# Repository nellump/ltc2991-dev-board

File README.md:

# LTC2991 Development Board

A simple printed circuit board that makes it easy to plug the
surface-mount (MSOP-16) [LTC2991][1] into a common breadboard.

[1]: http://www.linear.com/product/LTC2991

*NB: This project is a work in progress!  Schematic and PCB layout for
Rev. B design are complete; assembly is pending.*

## Features

* A pair of pin headers for each of the LTC2991's address lines.
  Jumpering the pins on any given address line connects that line to
  ground.
* Pads suitable for a current-sensing shunt resistor (1206 SMD),
  connected across the V1 and V2 terminals of the LTC2991, and pads
  for a 1x2 pin header to connect said shunt to the outside world.
* Pads suitable for a temperature-sensing, diode-connected NPN BJT
  (SOT-23 SMD), connected across the V3 and V4 terminals of the
  LTC2991, and a filter capactitor for said transistor.

## Caveats

There seems to be no such thing as a breadboard standard.  This PCB
was designed to work with an [R.S.R.-branded breadboard][2].  It
features a 0.100" pin pitch, and an approx. 0.300" gap down the middle
of the board.

[2]: http://rsrelectronics.com/breadboards.html

## Changelog

1. Rev. A: Initial design.
2. Rev. B:
  * Added two-pin header for measurement of external current source
    via on-board shunt resistor (both optional).
  * Added filter capacitor for IC power.
  * Added filter capacitor for temperature-sensing transistor (both
    optional).
  * Placed noise-shielding traces around temperature-sensing
    transistor.

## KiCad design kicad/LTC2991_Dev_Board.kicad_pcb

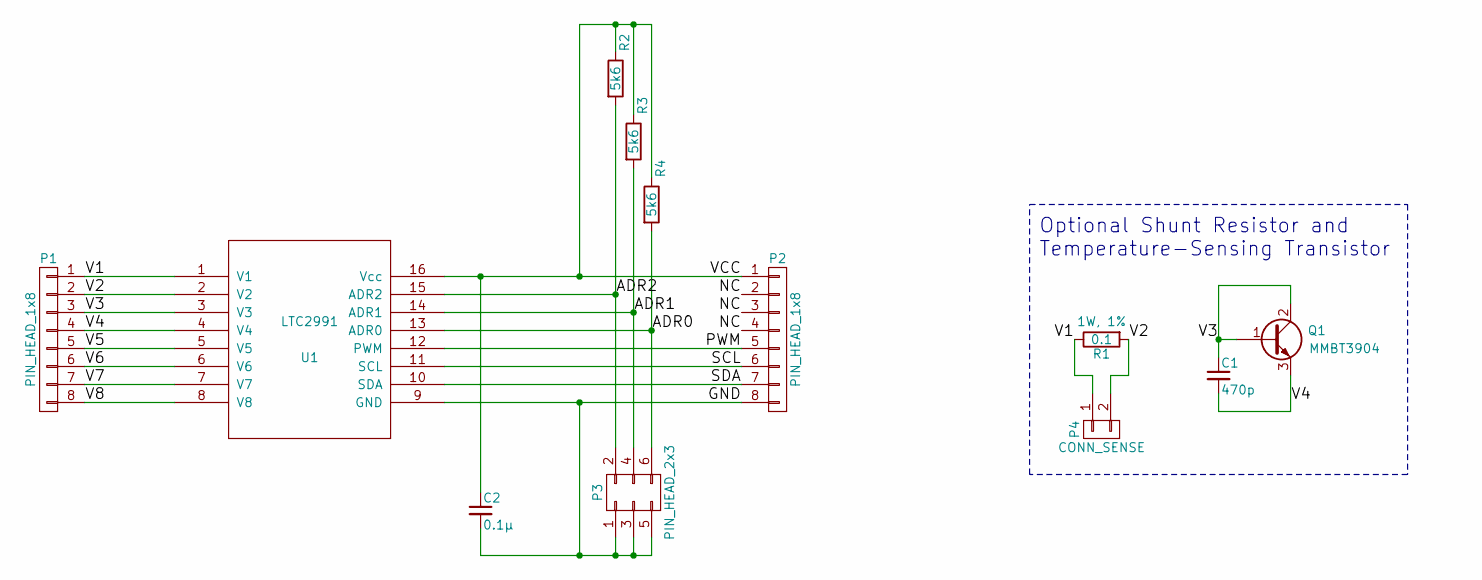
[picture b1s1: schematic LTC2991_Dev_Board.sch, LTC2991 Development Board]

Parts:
C1: 470p; C_0402
C2: 0.1μ; C_0402
P1, P2: PIN_HEAD_1x8; Pin_Header_Straight_1x08
P3: PIN_HEAD_2x3; Pin_Header_Straight_2x03
P4: CONN_SENSE; Pin_Header_Straight_1x02
Q1: MMBT3904; SOT-23
R1: 0.1; R_1206
R2, R3, R4: 5k6; R_0603
U1: LTC2991; MSOP-16

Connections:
/ADR0: P3.6, R4.2, U1.13 (ADR0)
/ADR1: P3.4, R3.2, U1.14 (ADR1)
/ADR2: P3.2, R2.2, U1.15 (ADR2)
/GND: C2.2, P2.8, P3.1, P3.3, P3.5, U1.9 (GND)
/NC: P2.2, P2.3, P2.4
/PWM: P2.5, U1.12 (PWM)
/SCL: P2.6, U1.11 (SCL)
/SDA: P2.7, U1.10 (SDA)
/V1: P1.1, P4.1, R1.1, U1.1 (V1)
/V2: P1.2, P4.2, R1.2, U1.2 (V2)
/V3: C1.1, P1.3, Q1.1 (B), Q1.2 (C), U1.3 (V3)
/V4: C1.2, P1.4, Q1.3 (E), U1.4 (V4)
/V5: P1.5, U1.5 (V5)
/V6: P1.6, U1.6 (V6)
/V7: P1.7, U1.7 (V7)
/V8: P1.8, U1.8 (V8)
/VCC: C2.1, P2.1, R2.1, R3.1, R4.1, U1.16 (Vcc)

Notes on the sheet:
Optional Shunt Resistor and Temperature-Sensing Transistor

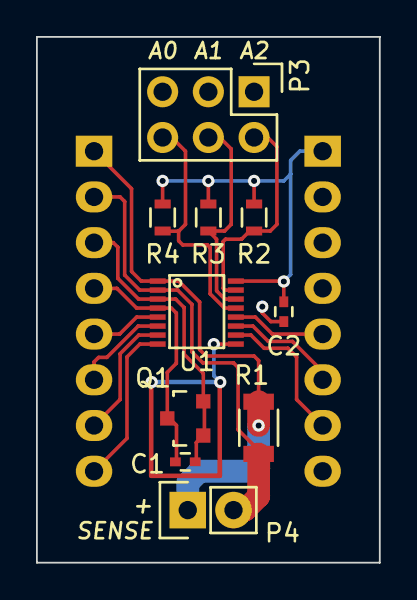
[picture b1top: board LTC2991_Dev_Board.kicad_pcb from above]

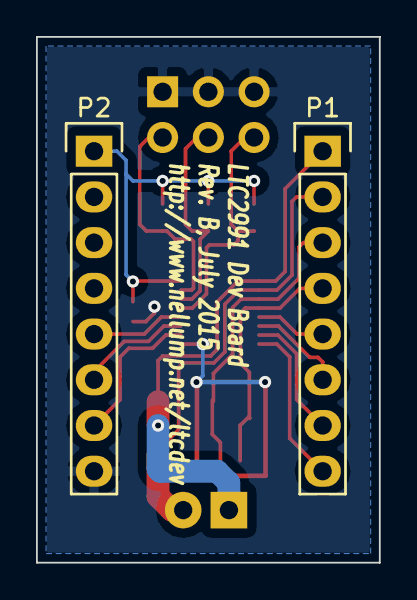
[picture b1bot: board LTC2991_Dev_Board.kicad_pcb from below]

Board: 2 copper layers, 19.1 x 29.2 mm, 12 parts (2 on the bottom side), 17 nets.

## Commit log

2015-07-12 First draft of dev board schematic.
2015-07-13 Beginning stages of PCB layout. Likely to need a few modifications to meet board size requirements.
2015-07-13 More PCB layout work, schematic tweaks. Closer to a finaly layout.
2015-07-15 Final schematic and PCB layout for Rev. A. Significantly simplified the schematic in order to make the board as compact as possible.
2015-07-15 Minor adjustment to PCB silkscreen. Added labels to pins in address jumper. Moved board name to front side.
2015-07-15 Moved Gerber files out of ./kicad/ and into the top level. Generated/compiled files should have their own home.
2015-07-15 Added README, PDF of schematic.
2015-07-16 Created Gerber for front side solder paste. Added it to the gerbv project file.
2015-07-18 Minor adjustments to text on PCB's back silkscreen.
2015-07-18 .gitignore edit.
2015-07-25 Updated README. Rev. A. is broken.
2015-07-26 Modified schematic and PCB layout. 1. Added two-pin header for measurement of external current source via on-board shunt resistor (both optional). 2. Added filter capacitor for IC power. 3. Added fil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
2015-07-26 Rearranged schematic. In the hopes of making it a bit more readable. Updated PCB layout with new netlist (no significant changes).
2015-07-26 Updated README, title blocks in KiCad drawings.
2015-07-26 Minor adjustment to back silk screen text.
2015-07-26 Grounded Faraday traces surrounding temp-sensing transistor.
2015-07-29 Converted README to reStructured Text.
2015-08-30 Updated README.
2015-09-30 Deleted unused symbols and footprints.
2015-12-04 Removed unused symbol library from schematic.
2016-12-10 Rearranged repo to match preferred hardware project layout.
2017-05-08 Updated .gitignore
2017-05-08 Cleaned up schematic for sake of readability. No functional changes.
2017-05-08 Updated README to reflect recent schematic changes.
2017-05-08 Removed link to schematic PDF from README.
    It did not work as expected with cgit.
